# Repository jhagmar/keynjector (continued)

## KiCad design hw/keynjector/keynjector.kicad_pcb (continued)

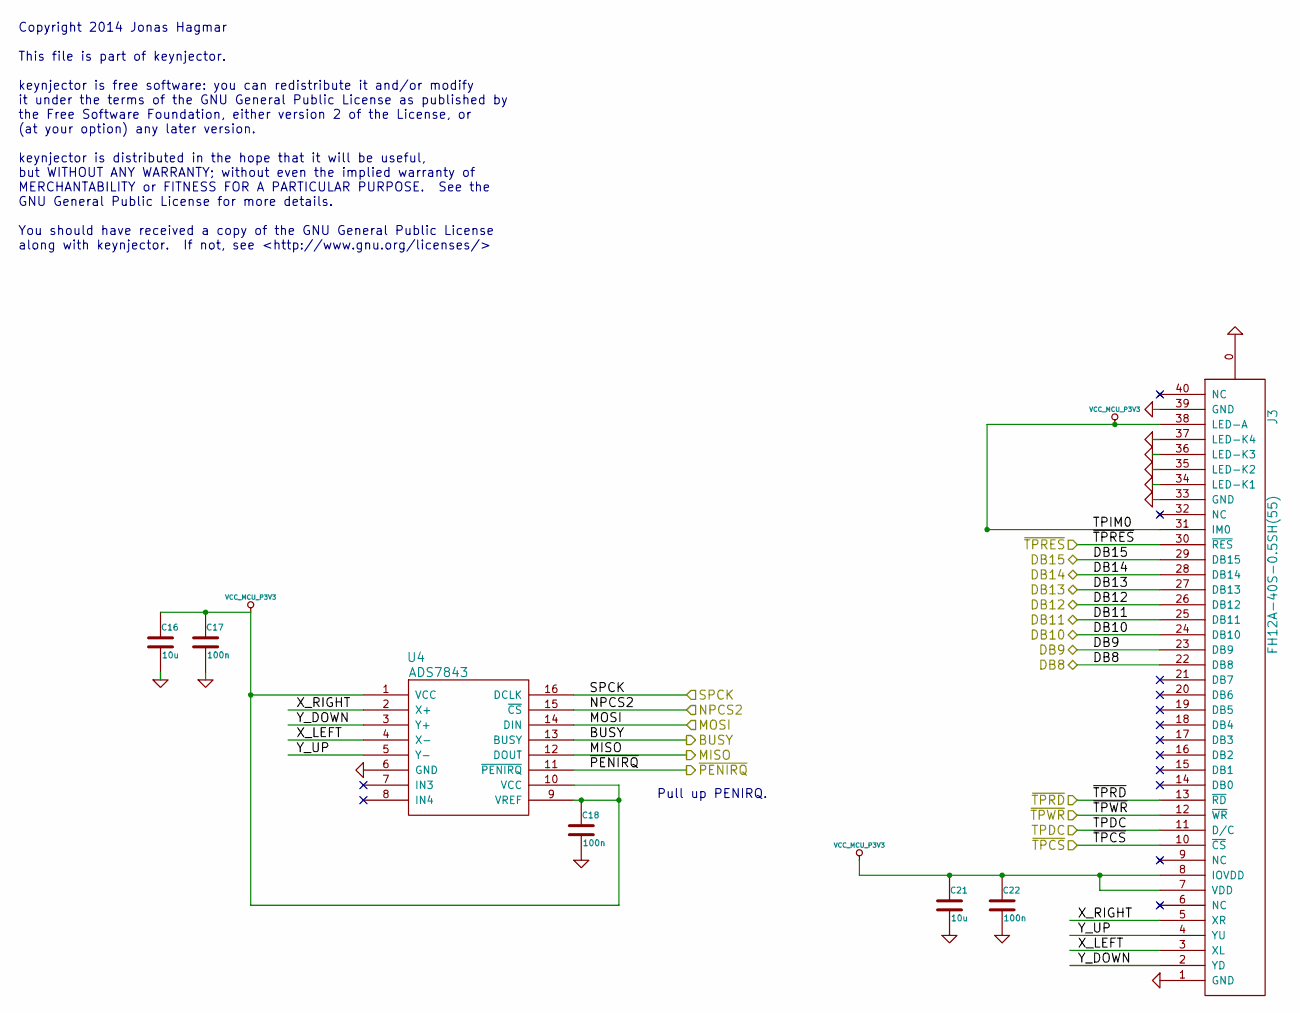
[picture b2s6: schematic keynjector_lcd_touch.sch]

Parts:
C16, C21: 10u
C17, C18, C22: 100n
J3: FH12A-40S-0.5SH(55)
U4: ADS7843

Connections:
/keynjector_lcd_touch/BUSY: U4.13 (BUSY); also elsewhere on the board
/keynjector_lcd_touch/DB8: J3.22 (DB8); also elsewhere on the board
/keynjector_lcd_touch/DB9: J3.23 (DB9); also elsewhere on the board
/keynjector_lcd_touch/DB10: J3.24 (DB10); also elsewhere on the board
/keynjector_lcd_touch/DB11: J3.25 (DB11); also elsewhere on the board
/keynjector_lcd_touch/DB12: J3.26 (DB12); also elsewhere on the board
/keynjector_lcd_touch/DB13: J3.27 (DB13); also elsewhere on the board
/keynjector_lcd_touch/DB14: J3.28 (DB14); also elsewhere on the board
/keynjector_lcd_touch/DB15: J3.29 (DB15); also elsewhere on the board
/keynjector_lcd_touch/MISO: U4.12 (DOUT); also elsewhere on the board
/keynjector_lcd_touch/MOSI: U4.14 (DIN); also elsewhere on the board
/keynjector_lcd_touch/NPCS2: U4.15 (~CS); also elsewhere on the board
/keynjector_lcd_touch/SPCK: U4.16 (DCLK); also elsewhere on the board
/keynjector_lcd_touch/TPDC: J3.11 (D/C); also elsewhere on the board
/keynjector_lcd_touch/X_LEFT: J3.3 (XL), U4.4 (X-)
/keynjector_lcd_touch/X_RIGHT: J3.5 (XR), U4.2 (X+)
/keynjector_lcd_touch/Y_DOWN: J3.2 (YD), U4.3 (Y+)
/keynjector_lcd_touch/Y_UP: J3.4 (YU), U4.5 (Y-)
/keynjector_lcd_touch/~PENIRQ: U4.11 (~PENIRQ); also elsewhere on the board
/keynjector_lcd_touch/~TPCS: J3.10 (~CS); also elsewhere on the board
/keynjector_lcd_touch/~TPRD: J3.13 (~RD); also elsewhere on the board
/keynjector_lcd_touch/~TPRES: J3.30 (~RES); also elsewhere on the board
/keynjector_lcd_touch/~TPWR: J3.12 (~WR); also elsewhere on the board
GND: C16.2, C17.2, C18.2, C21.2, C22.2, J3.0, J3.1 (GND), J3.33 (GND), J3.34 (LED-K1), J3.35 (LED-K2), J3.36 (LED-K3), J3.37 (LED-K4), J3.39 (GND), U4.6 (GND); also elsewhere on the board
VCC_MCU_P3V3: C16.1, C17.1, C18.1, C21.1, C22.1, J3.7 (VDD), J3.8 (IOVDD), J3.31 (IM0), J3.38 (LED-A), U4.1 (VCC), U4.9 (VREF), U4.10 (VCC); also elsewhere on the board

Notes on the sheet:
Pull up PENIRQ.
Copyright 2014 Jonas Hagmar This file is part of keynjector. keynjector is free software: you can redistribute it and/or modify it under the terms of the GNU General Public License as published by the Free Software Foundation, either version 2 of the License, or (at your option) any later version. 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

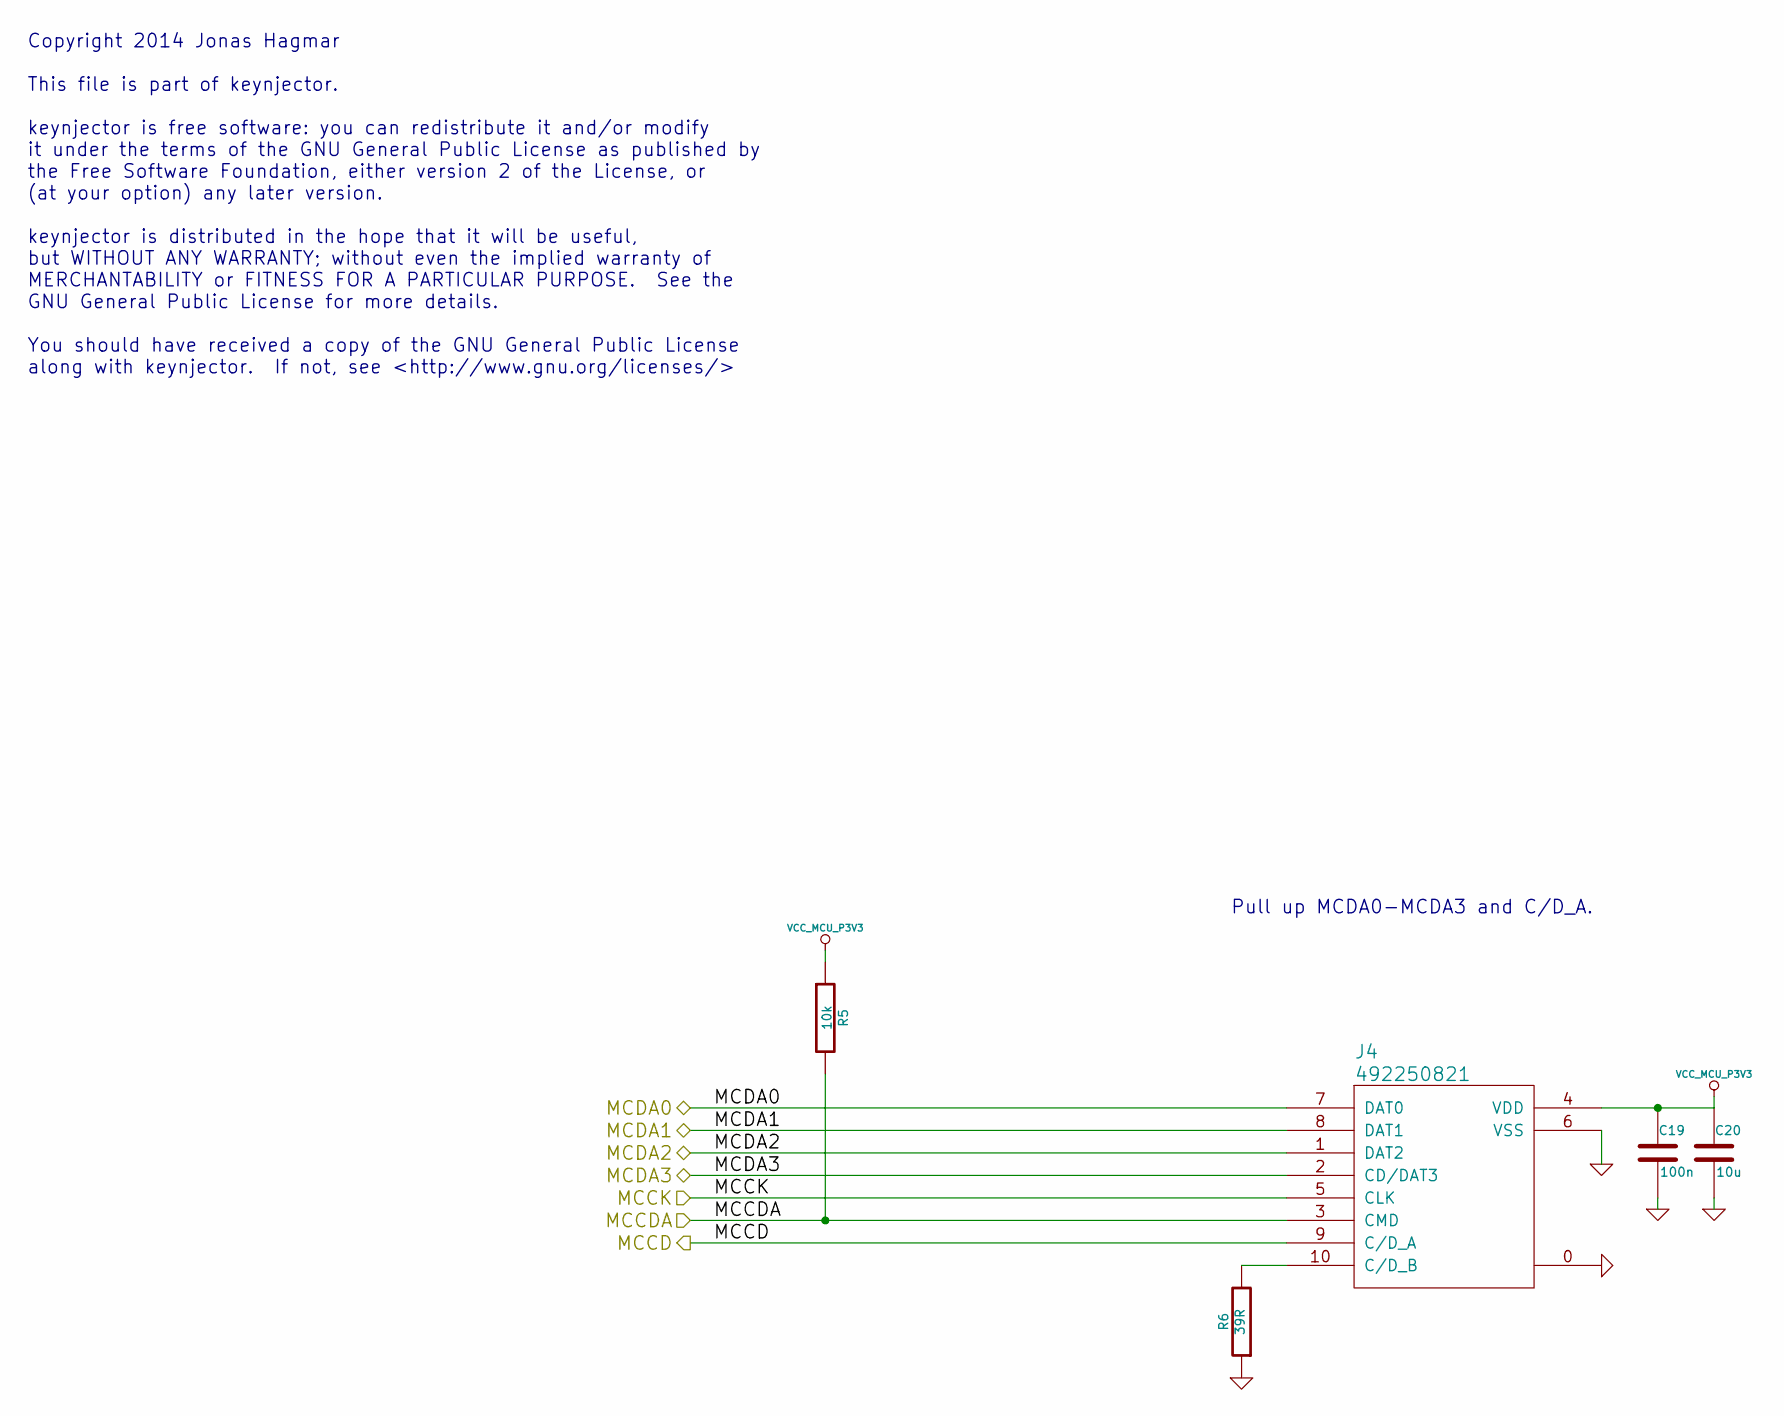
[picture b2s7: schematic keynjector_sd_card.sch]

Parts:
C19: 100n
C20: 10u
J4: 492250821
R5: 10k
R6: 39R

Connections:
/keynjector_mcu/MCCD: J4.9 (C/D_A); also elsewhere on the board
/keynjector_mcu/MCCDA: J4.3 (CMD), R5.2; also elsewhere on the board
/keynjector_mcu/MCCK: J4.5 (CLK); also elsewhere on the board
/keynjector_mcu/MCDA0: J4.7 (DAT0); also elsewhere on the board
/keynjector_mcu/MCDA1: J4.8 (DAT1); also elsewhere on the board
/keynjector_mcu/MCDA2: J4.1 (DAT2); also elsewhere on the board
/keynjector_mcu/MCDA3: J4.2 (CD/DAT3); also elsewhere on the board
GND: C19.2, C20.2, J4.0, J4.6 (VSS), R6.1; also elsewhere on the board
unnamed: J4.10 (C/D_B), R6.2
VCC_MCU_P3V3: C19.1, C20.1, J4.4 (VDD), R5.1; also elsewhere on the board

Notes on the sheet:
Pull up MCDA0-MCDA3 and C/D_A.
Copyright 2014 Jonas Hagmar This file is part of keynjector. keynjector is free software: you can redistribute it and/or modify it under the terms of the GNU General Public License as published by the Free Software Foundation, either version 2 of the License, or (at your option) any later version. 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

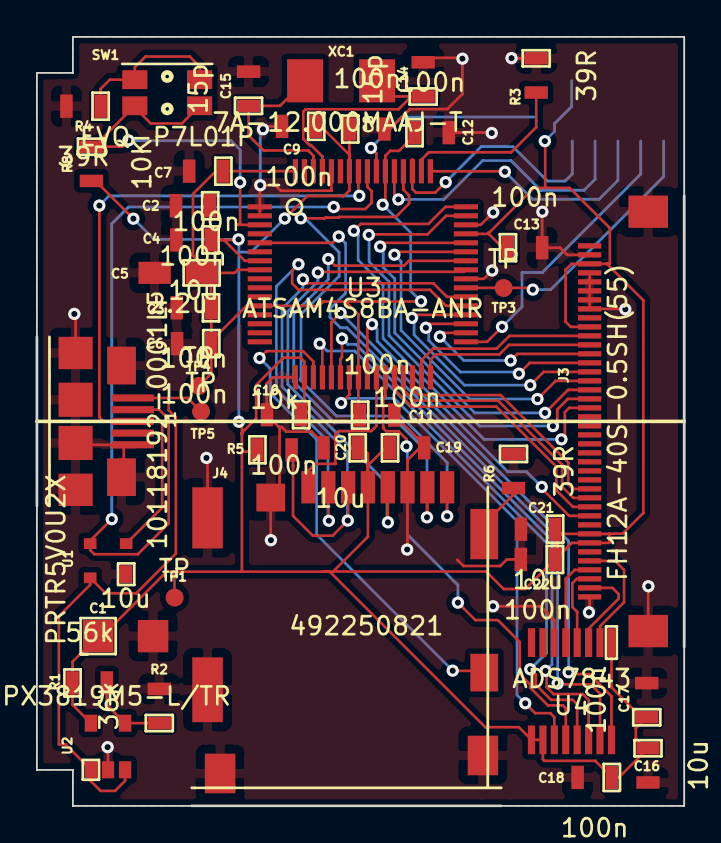
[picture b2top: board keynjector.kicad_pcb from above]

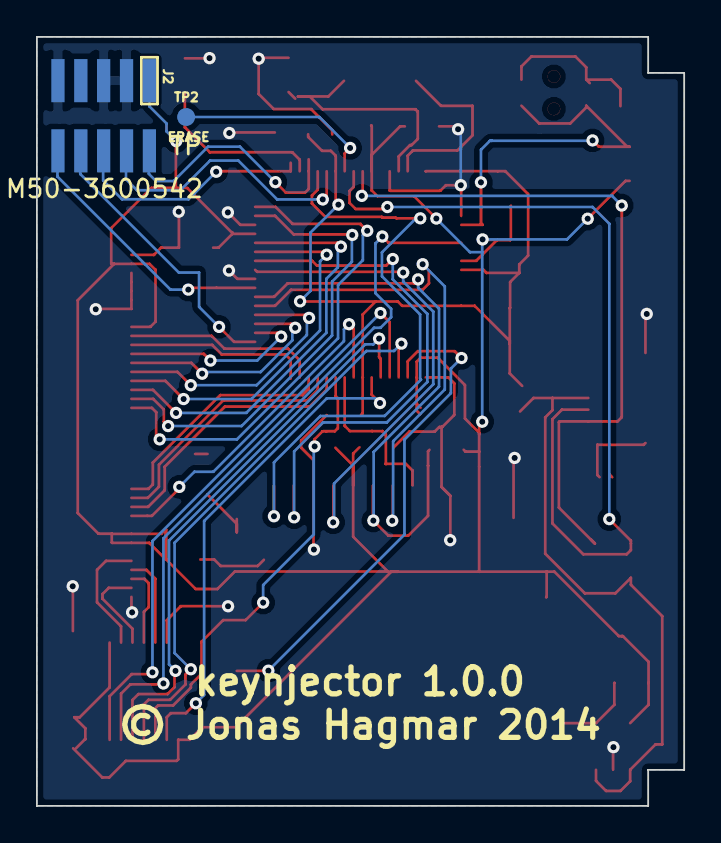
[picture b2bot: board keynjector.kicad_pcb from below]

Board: 2 copper layers, 36.0 x 42.7 mm, 44 parts (2 on the bottom side), 49 nets.

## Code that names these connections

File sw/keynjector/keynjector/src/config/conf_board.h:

/**
 * \file
 *
 * \brief User board configuration template
 *
 */

#ifndef CONF_BOARD_H
#define CONF_BOARD_H

#define ACCESS_MEM_TO_RAM_ENABLED

/** Board oscillator settings */
#define BOARD_FREQ_SLCK_XTAL        (32768U)
#define BOARD_FREQ_SLCK_BYPASS      (32768U)
#define BOARD_FREQ_MAINCK_XTAL      (12000000U)
#define BOARD_FREQ_MAINCK_BYPASS    (12000000U)

/** board main clock xtal startup time */
#define BOARD_OSC_STARTUP_US   15625

#define TP_RESET    PIO_PA8_IDX
#define TP_READ		PIO_PA9_IDX
#define TP_WRITE	PIO_PA10_IDX
#define TP_DC		PIO_PA11_IDX
#define TP_CS		PIO_PA25_IDX
#define TP_DATA_PORT	IOPORT_PIOA
#define TP_DATA_MASK	0x000000FF

/** HSMCI pins definition. */
/*! Number of slot connected on HSMCI interface */
#define SD_MMC_HSMCI_MEM_CNT      1
#define SD_MMC_HSMCI_SLOT_0_SIZE  4
#define PINS_HSMCI   {0x3fUL << 26, PIOA, ID_PIOA, PIO_PERIPH_C, PIO_PULLUP}
/** HSMCI MCCDA pin definition. */
#define PIN_HSMCI_MCCDA_GPIO            (PIO_PA28_IDX)
#define PIN_HSMCI_MCCDA_FLAGS           (PIO_PERIPH_C | PIO_DEFAULT)
/** HSMCI MCCK pin definition. */
#define PIN_HSMCI_MCCK_GPIO             (PIO_PA29_IDX)
#define PIN_HSMCI_MCCK_FLAGS            (PIO_PERIPH_C | PIO_DEFAULT)
/** HSMCI MCDA0 pin definition. */
#define PIN_HSMCI_MCDA0_GPIO            (PIO_PA30_IDX)
#define PIN_HSMCI_MCDA0_FLAGS           (PIO_PERIPH_C | PIO_PULLUP)
/** HSMCI MCDA1 pin definition. */
#define PIN_HSMCI_MCDA1_GPIO            (PIO_PA31_IDX)
#define PIN_HSMCI_MCDA1_FLAGS           (PIO_PERIPH_C | PIO_PULLUP)
/** HSMCI MCDA2 pin definition. */
#define PIN_HSMCI_MCDA2_GPIO            (PIO_PA26_IDX)
#define PIN_HSMCI_MCDA2_FLAGS           (PIO_PERIPH_C | PIO_PULLUP)
/** HSMCI MCDA3 pin definition. */
#define PIN_HSMCI_MCDA3_GPIO            (PIO_PA27_IDX)
#define PIN_HSMCI_MCDA3_FLAGS           (PIO_PERIPH_C | PIO_PULLUP)
/** SD/MMC card detect pin definition. */

#define PIN_HSMCI_CD {PIO_PA16, PIOA, ID_PIOA, PIO_INPUT, PIO_PULLUP, PIO_DEBOUNCE}
#define SD_MMC_0_CD_GPIO            (PIO_PA16_IDX)
#define SD_MMC_0_CD_PIO_ID          ID_PIOA
#define SD_MMC_0_CD_FLAGS           (PIO_INPUT | PIO_PULLUP)
#define SD_MMC_0_CD_DETECT_VALUE    0

#define CONF_BOARD_SD_MMC_HSMCI

/** Touchscreen controller IRQ & Busy pin definition. */
#define BOARD_ADS7843_IRQ_GPIO      PIO_PA24_IDX
#define BOARD_ADS7843_IRQ_FLAGS     PIO_INPUT | PIO_PULLUP
#define BOARD_ADS7843_IRQ_WUP_ID    (1 << 15)
#define BOARD_ADS7843_BUSY_GPIO     PIO_PA15_IDX
#define BOARD_ADS7843_BUSY_FLAGS    PIO_INPUT | PIO_PULLUP

#define CONF_BOARD_ADS7843

/** Base address of SPI peripheral connected to the touchscreen controller. */
#define BOARD_ADS7843_SPI_BASE      SPI
/** Identifier of SPI peripheral connected to the touchscreen controller. */
#define BOARD_ADS7843_SPI_ID        ID_SPI
/** Chip select connected to the touchscreen controller. */
#define BOARD_ADS7843_SPI_NPCS      2

/** SPI MISO pin definition. */
#define SPI_MISO_GPIO             (PIO_PA12_IDX)
#define SPI_MISO_FLAGS       (PIO_PERIPH_A | PIO_DEFAULT)
/** SPI MOSI pin definition. */
#define SPI_MOSI_GPIO             (PIO_PA13_IDX)
#define SPI_MOSI_FLAGS       (PIO_PERIPH_A | PIO_DEFAULT)
/** SPI SPCK pin definition. */
#define SPI_SPCK_GPIO             (PIO_PA14_IDX)
#define SPI_SPCK_FLAGS       (PIO_PERIPH_A | PIO_DEFAULT)

#define SPI_NPCS2_PB2_GPIO        (PIO_PB2_IDX)
#define SPI_NPCS2_PB2_FLAGS       (PIO_PERIPH_B | PIO_DEFAULT)

#endif // CONF_BOARD_H

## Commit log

2014-11-22 added initial version of case
2014-11-22 added datasheets
2014-11-22 added keynjector Atmel Studio project
2014-11-22 added fonts
2014-11-22 added keynjector ui testbench
2014-11-23 added keynjector KiCad project
2014-11-24 * revised ignored files * added missing file
2014-11-25 added bill of materials
2014-11-25 added zifbrkout KiCad project
2014-11-25 adjusted ignore for KiCad backup files
2014-11-26 * removed logo from key screen * added up/down buttons to scroll key screen
2014-11-29 improved case with holes for screws and nuts
2014-12-02 added license text to KiCad sheets
2014-12-02 moved debug header to board back to facilitate debug with board in case
2014-12-03 moved erase testpoint to back to facilitate debugging/reprogramming in debug case adjusted version number on PCB to 1.0.0 for first real release
2014-12-04 added comments adjusted code to serve as library
2014-12-04 added screen support
2014-12-04 changed edge cuts to accomodate for screen support
2014-12-05 added copyright notices added COPYING file with GPL v2 license added README file moved font files
2014-12-05 revised README added AUTHORS
2014-12-05 added OpenSCAD files to generate parts suitable for 3D printing added a simple .bat build file for case parts
2014-12-07 renamed COPYING to LICENSE added information to README
2015-02-04 added missing includes for C99 types
2015-02-04 revised debug case due to collision of debug connector with case in test print
2015-03-24 changed keynjector case after feedback from 3D printing
